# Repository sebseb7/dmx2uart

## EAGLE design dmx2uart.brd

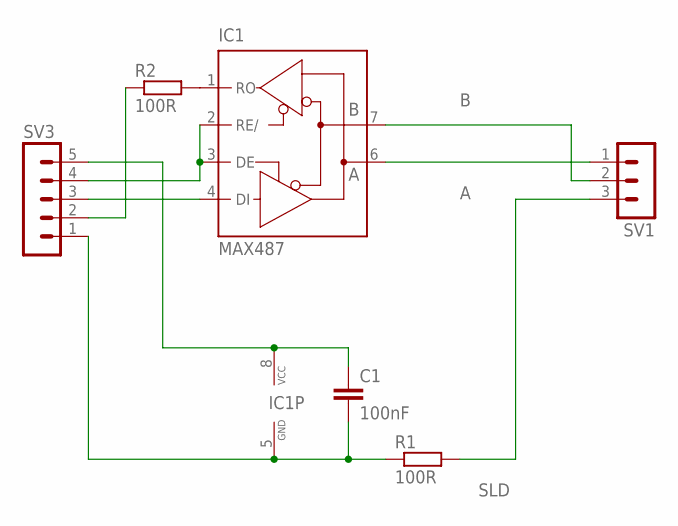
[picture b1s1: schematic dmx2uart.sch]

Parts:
C1: 100nF; C075-032X103
IC1: MAX487; DIL08
R1: 100R; 0207/7
R2: 100R; 0207/10
SV1: MA03-1
SV3: MA05-1

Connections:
A: IC1.6 (A), SV1.1
B: IC1.7 (B), SV1.2
unnamed: C1.2, IC1.5 (GND), R1.1, SV3.1
unnamed: C1.1, IC1.8 (VCC), SV3.5
unnamed: IC1.1 (RO), R2.2
unnamed: R2.1, SV3.2
unnamed: IC1.2 (RE/), IC1.3 (DE), SV3.4
unnamed: IC1.4 (DI), SV3.3
SLD: R1.2, SV1.3

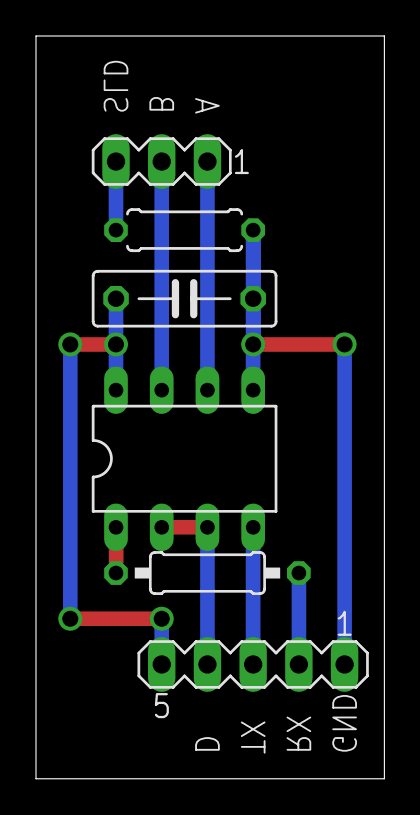
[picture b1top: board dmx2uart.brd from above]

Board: 2 copper layers, 19.4 x 41.3 mm, 6 parts (0 on the bottom side), 9 nets.

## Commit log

2016-09-25 init
2016-09-25 readme
2016-09-26 capacitor size
